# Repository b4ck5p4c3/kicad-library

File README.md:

# B4CKSP4CE KiCAD Library 🪚

## Installation

1. Install latest version of [KiCAD](https://www.kicad.org/download/).

2. Clone this repository in persistent folder on your machine.
   You'll need it every time you use KiCAD.

3. Open KiCAD. In the main window, go to `Preferences` > `Configure Paths...`.

4. Add a new variable called `KICAD_BKSP_LIB_DIR` and set its value to the full path
   of `library` folder in the cloned repository.

   Example: `/Users/Resident/BKSP/kicad-library/library`.

5. In the same window, go to `Preferences` > `Manage Footprint Libraries...`.
   In the `Global Libraries` tab, click on "+" button. Set **Nickname** to `BKSP` and **Library Path** to `${KICAD_BKSP_LIB_DIR}/BKSP.pretty`
   Click `OK` to add the library.

6. Repeat the previous step, but this time for `Manage Symbol Libraries...`.
   Set **Nickname** to `BKSP` and **Library Path** to `${KICAD_BKSP_LIB_DIR}/BKSP.kicad_sym`

7. Once more for `Manage Design Block Libraries...`.
   Set **Nickname** to `BKSP` and **Library Path** to `${KICAD_BKSP_LIB_DIR}/BKSP.kicad_blocks`

## License

This project is licensed under the MIT License - see the [LICENSE](LICENSE) file for details.

Note that parts of this repository might be licensed under different licenses.
As B4CKSP4CE don't endorse commercial use of this repository, we consider it safe to use them.
Althrough, we recommend to check the license of each part before using it in your project.

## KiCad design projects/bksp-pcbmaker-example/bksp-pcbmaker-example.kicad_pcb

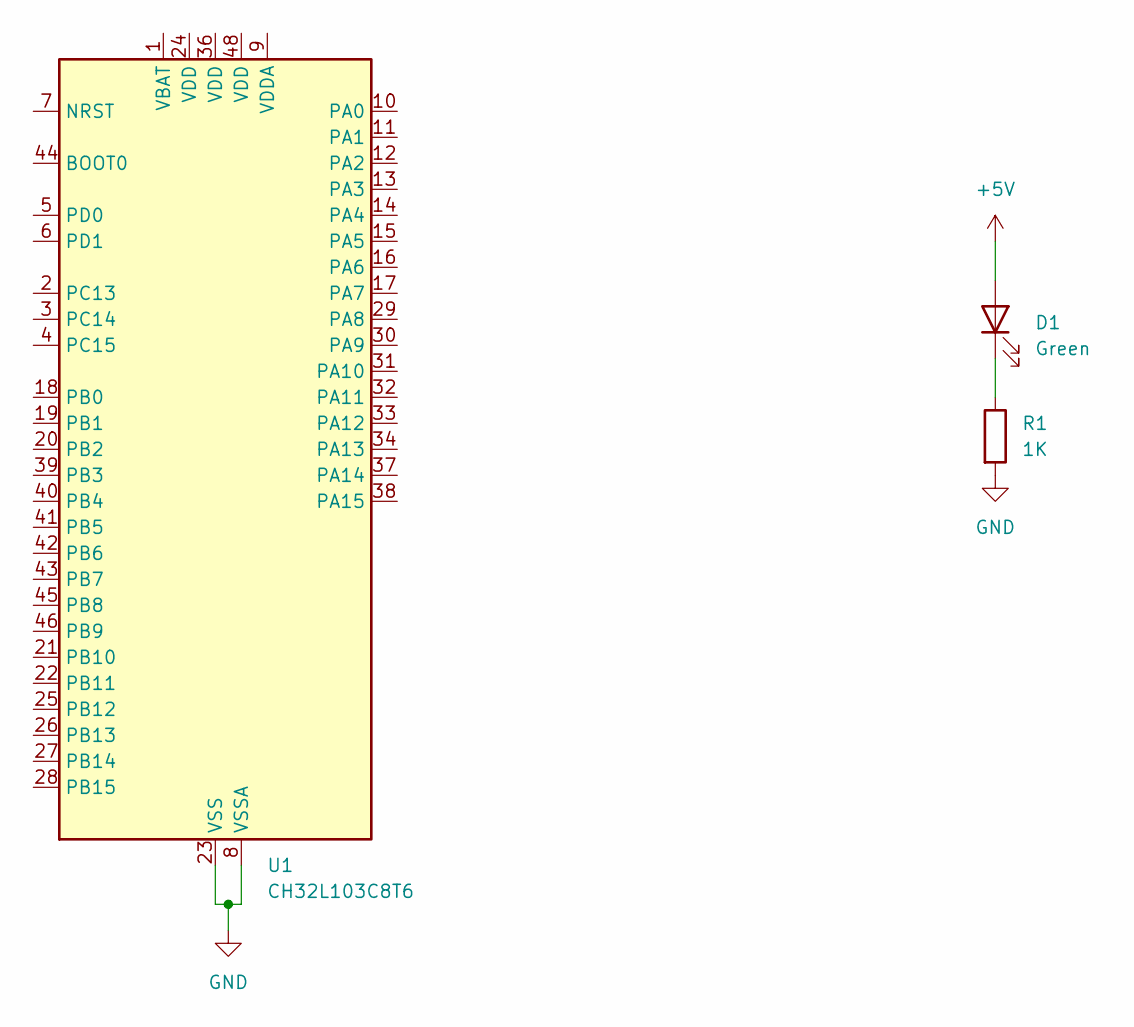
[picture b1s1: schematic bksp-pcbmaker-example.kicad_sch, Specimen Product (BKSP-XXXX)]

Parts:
D1: Green; LED_1206_3216Metric
R1: 1K; R_0805_2012Metric
U1: CH32L103C8T6; LQFP-48_7x7mm_P0.5mm

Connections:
+5V: D1.2 (A)
GND: R1.2, U1.8 (VSSA), U1.23 (VSS), U1.35 (VSS), U1.47 (VSS)
unnamed: D1.1 (K), R1.1

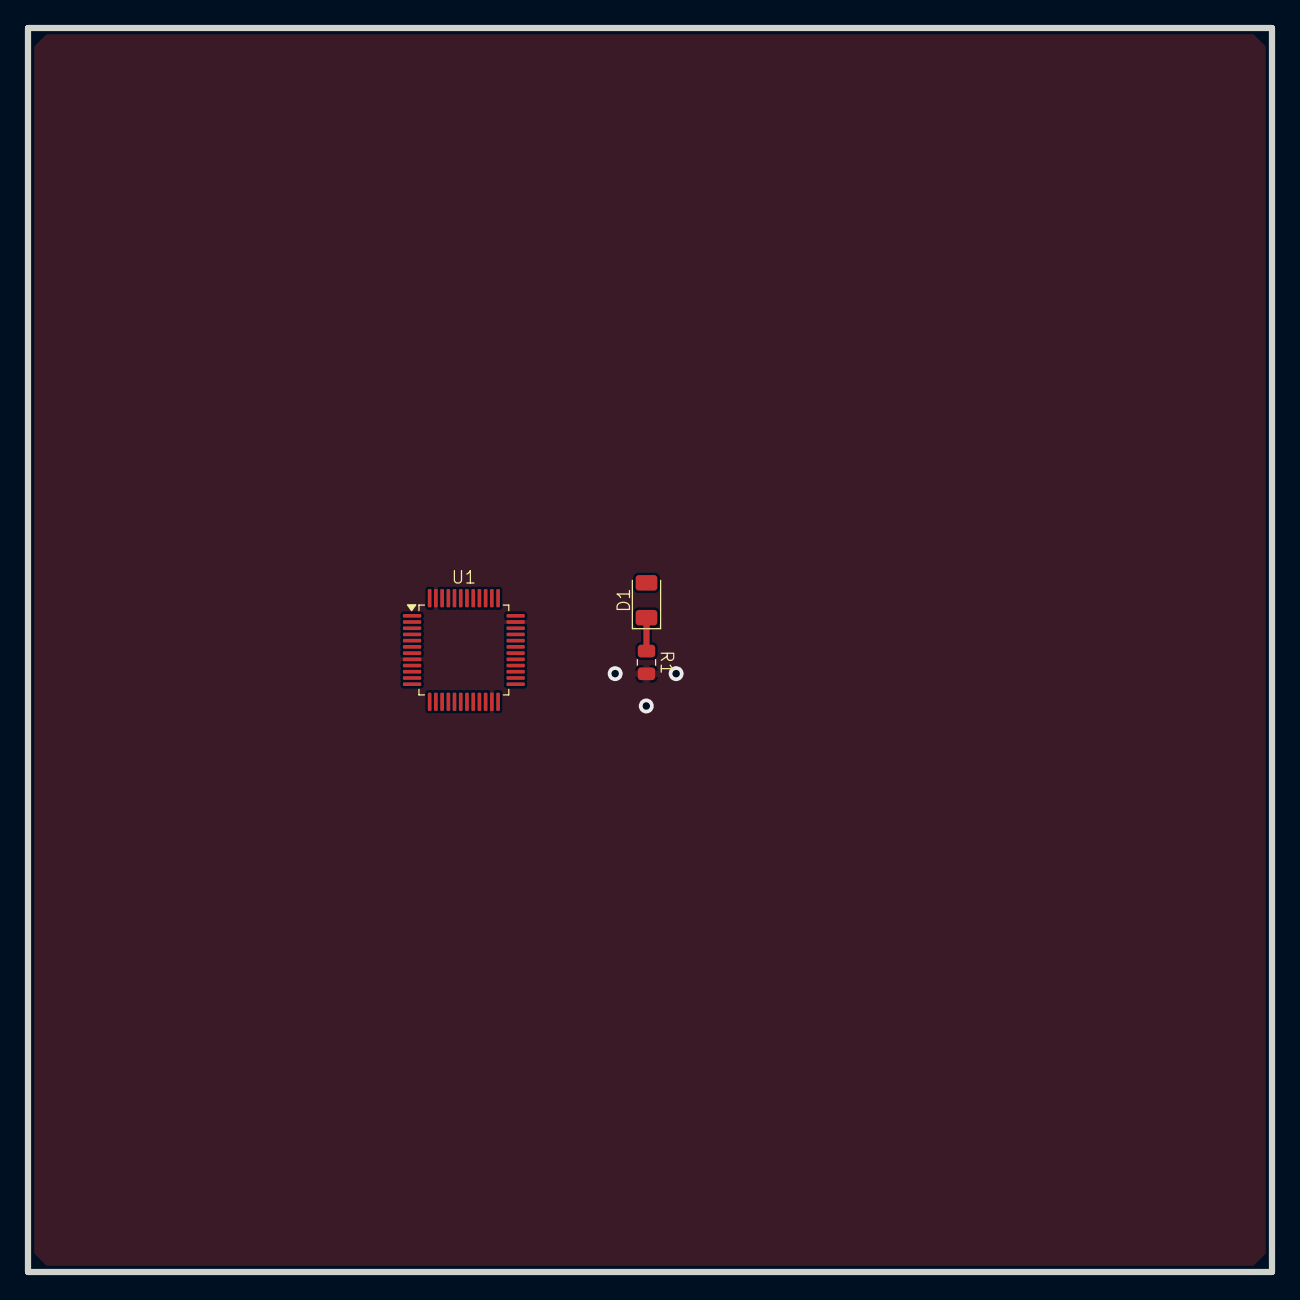
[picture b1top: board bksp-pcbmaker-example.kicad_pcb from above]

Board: 2 copper layers, 100.0 x 100.0 mm, 3 parts (0 on the bottom side), 2 nets.

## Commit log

2025-04-18 feat: initial
2025-05-06 feat(symbols): re-arrange library
2025-05-07 feat(reference): update DRC & Copper Fill settings in a reference project
2025-05-07 feat(lib): add footprint for SFP connector without cage
2025-06-19 feat: add CAM-M8Q symbol, footprint, and 3D model
2025-08-22 feat(symbols): add EByte E22-M Series, IPEX, and thermal-relieved via

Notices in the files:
projects/bksp-pcbmaker-example/bksp-pcbmaker-example.kicad_pcb:
CERN-OHL-S
